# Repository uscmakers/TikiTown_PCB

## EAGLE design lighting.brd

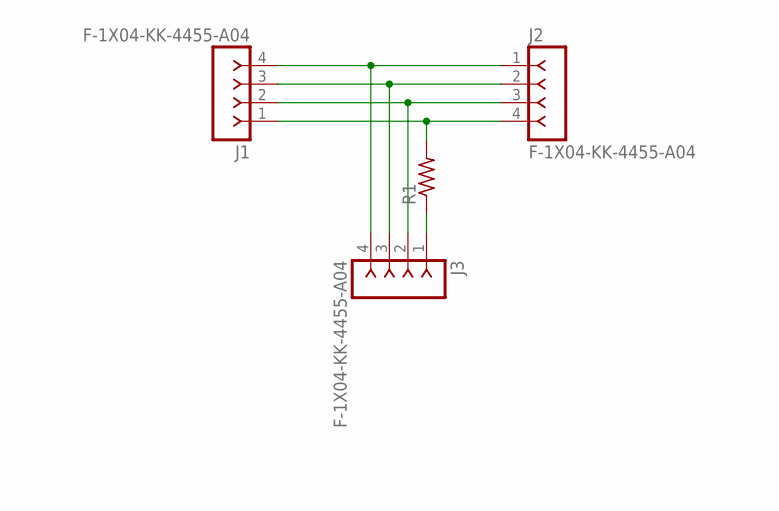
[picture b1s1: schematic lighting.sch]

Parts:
J1, J2, J3: F-1X04-KK-4455-A04; KK-4455-A04
R1: R-US_0207/12; 0207/12

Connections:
unnamed: J1.4, J2.1, J3.4
unnamed: J1.3, J2.2, J3.3
unnamed: J1.2, J2.3, J3.2
unnamed: J1.1, J2.4, R1.2
unnamed: J3.1, R1.1

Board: 2 copper layers, 4 parts (0 on the bottom side), 5 nets, no tracks yet.

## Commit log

2018-02-06 bt module connected with arduino and accelerometer
2018-02-07 finish initial design of lighting system

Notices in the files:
parts and their libraries:
con-headers-jp: Copyright (C) 2008, Bob Starr
